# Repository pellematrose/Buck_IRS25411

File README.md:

# Buck_IRS25411
High Voltage Buck featuring IRS25411 LED driver.

The pinheaders offers the opportunity to use it as module on a other PCB.

The IRS25411 is a hysteretic Buck driver for LED applications.
Hysteretic means that there is no fixed frequency but it switches with over and undershooting the threshold level of the feedback pin with the current ripple.
Due to the feedback voltage of 0.5V it is not worth driving more than 1A of current. The needed current sensing resistor results to R = 0.5V / 1A = 0.5Ohms. The power losses are Pls = 0.5V * 1A = 0.5W. This is already to much for a standard 1206 resistor. Using multiple resistors in parallel it might work.

In this design the current sensing resistor moved directly behind the inductor and a op-amp is driving a pnp transistor to provide an appropriate voltage to the feedback pin. Thus, a constant current is maintained.
Additionally, an other part of the circuitry around the TS431 is regulating the voltage.

In parallel operation both CC and CV regulators are active. When the maximum current is flowing the voltage drops and the buck is working in CC mode.
When the maximum current is not flowing the voltage is clipped at the voltage set and the buck is working in CV mode.

The schematic offers the opportunity to assemble the pcb in three ways:
1. Infineon typical application with low side shunt (tested and works)
2. High current CC mode with the op-amp
3. CV mode with TS431 (tested and works)
4. Combined high current CC and CV mode

The design contains a routing mistake:
The connection between VS and Inductor is missing.

Schematics:
1. Infineon typical application with low side shunt

2. High current CC mode with the op-amp

3. CV mode with TS431

4. Combined high current CC and CV mode

To make it easy to adjust some component values the excel file may help you understand how the values are calculated.

I got the main inspiration from various application notes about the buck converter.  
[TI CC CV converter](https://www.ti.com/lit/an/snva829/snva829.pdf)  
[Electronics Stackexchange](https://electronics.stackexchange.com/questions/458384/cc-cv-buck-controller)  
[Buck converter design](https://www.mouser.de/pdfdocs/BuckConverterDesignNote.pdf)

Furthermore, here some links to usefull sites about mosfet losses:  
[Infineon MOSFET Losses Appnote](https://community.infineon.com/gfawx74859/attachments/gfawx74859/MOSFET/285/4/MOSFET%20Power%20Losses%20Calculation%20Using%20the%20Data-Sheet%20Parameters.pdf)  
[Youtube with Dr. K](https://www.youtube.com/watch?v=RViwOc4g-gw)</p>

The Buck design is only tested to 30V input voltage.
If you want to make a real high voltage buck you need to recalculate some components:
- R1 to limit the input current to the driver IC
- Q1, Q2 MOSFET Vds rating
- L1 Inductor
- Supply for the OpAmp (only ratet up to 30V)

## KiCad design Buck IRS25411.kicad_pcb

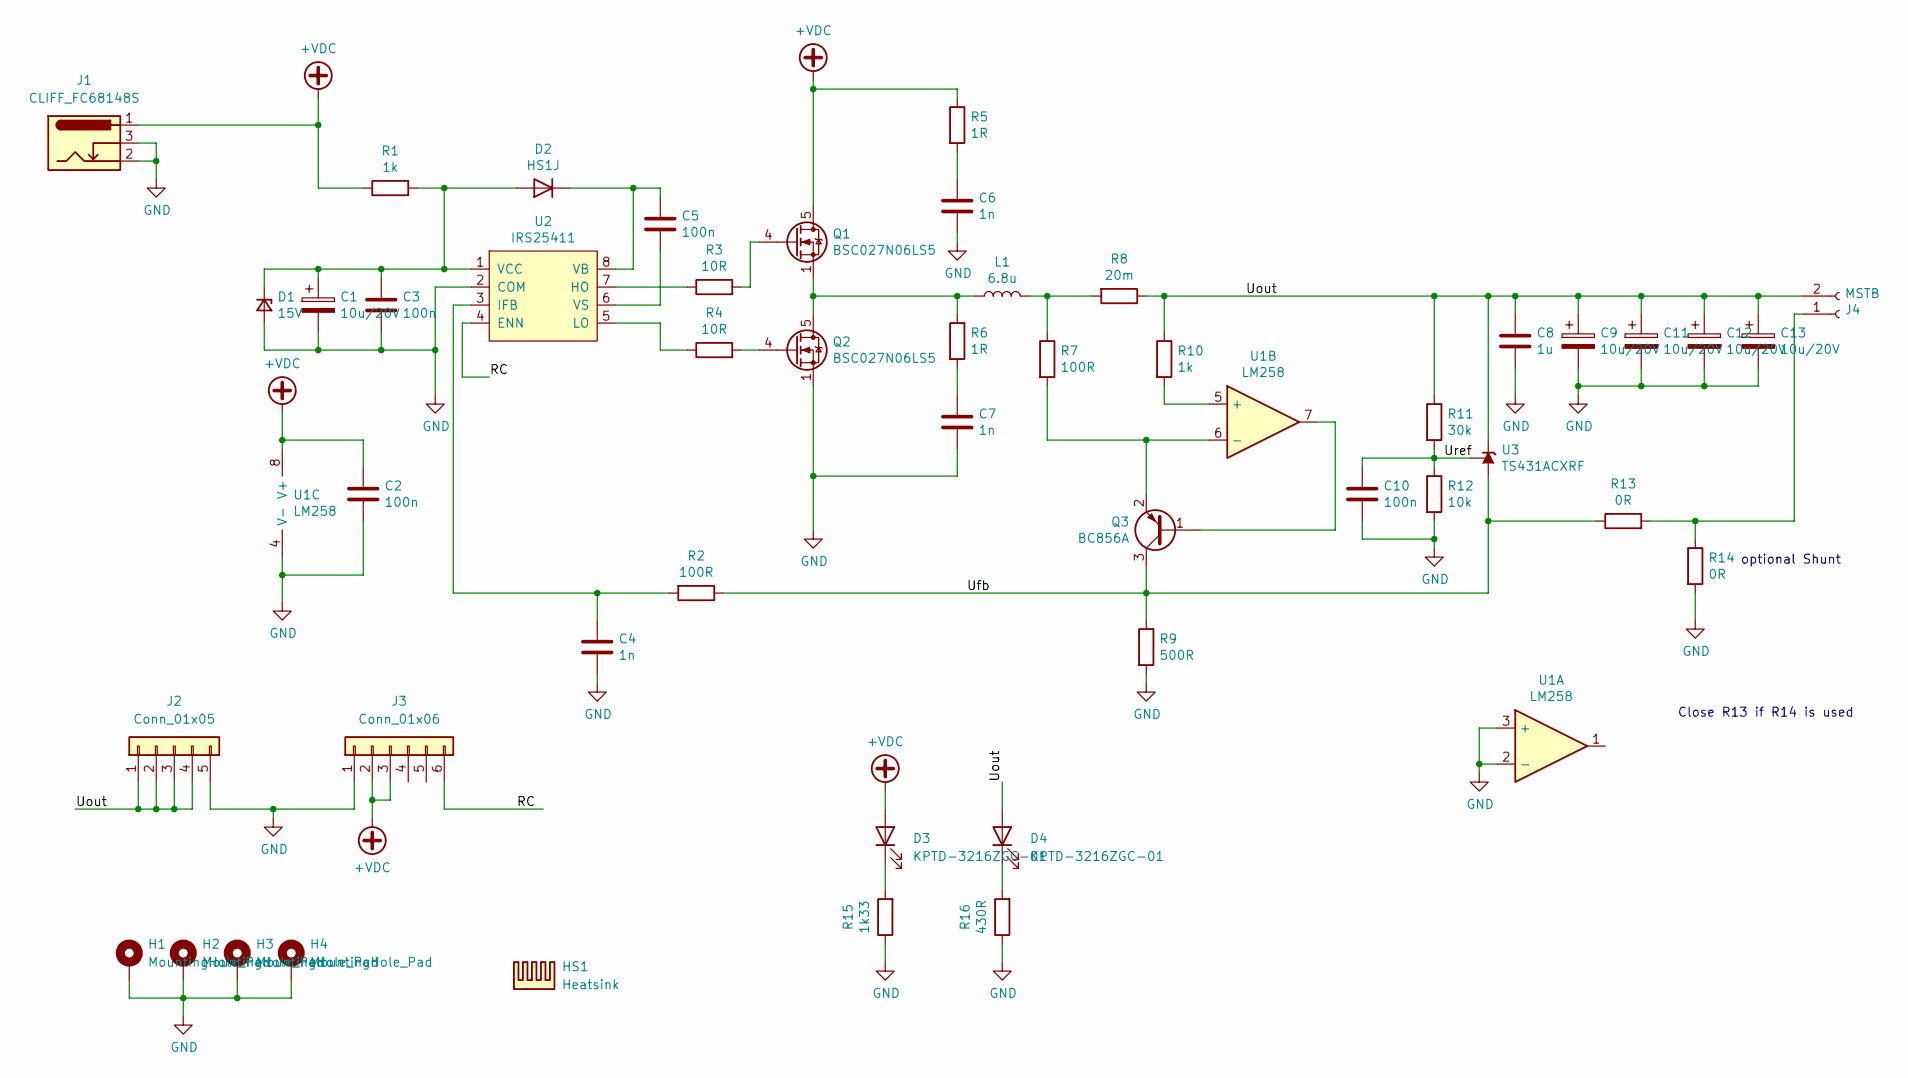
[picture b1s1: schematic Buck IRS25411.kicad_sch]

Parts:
C1, C9, C11, C12, C13: 10u/20V; CP_EIA-3216-18_Kemet-A_Pad1.58x1.35mm_HandSolder
C2, C3, C5, C10: 100n; C_0805_2012Metric_Pad1.18x1.45mm_HandSolder
C4: 1n; C_0603_1608Metric_Pad1.08x0.95mm_HandSolder
C6, C7: 1n; C_1206_3216Metric_Pad1.33x1.80mm_HandSolder
C8: 1u; C_0805_2012Metric_Pad1.18x1.45mm_HandSolder
D1: 15V; D_SOD-123F
D2: HS1J; D_SMA_Handsoldering
D3, D4: KPTD-3216ZGC-01; LED_1206_3216Metric_Pad1.42x1.75mm_HandSolder
H1, H2, H3, H4: MountingHole_Pad; MountingHole_2.2mm_M2_DIN965_Pad_TopBottom
HS1: Heatsink
J1: CLIFF_FC68148S; BarrelJack_CLIFF_FC681465S_SMT_Horizontal
J2: Conn_01x05; PinHeader_1x05_P2.54mm_Horizontal
J3: Conn_01x06; PinHeader_1x06_P2.54mm_Horizontal
J4: MSTB; PhoenixContact_MC_1,5_2-G-5.08_1x02_P5.08mm_Horizontal
L1: 6.8u; L_Bourns_SRR1260
Q1, Q2: BSC027N06LS5; TDSON-8-1
Q3: BC856A; SOT-23
R1, R10: 1k; R_0603_1608Metric_Pad0.98x0.95mm_HandSolder
R2, R7: 100R; R_0603_1608Metric_Pad0.98x0.95mm_HandSolder
R3, R4: 10R; R_0603_1608Metric_Pad0.98x0.95mm_HandSolder
R5, R6: 1R; R_1206_3216Metric_Pad1.30x1.75mm_HandSolder
R8: 20m; R_1206_3216Metric_Pad1.30x1.75mm_HandSolder
R9: 500R; R_0603_1608Metric_Pad0.98x0.95mm_HandSolder
R11: 30k; R_0603_1608Metric_Pad0.98x0.95mm_HandSolder
R12: 10k; R_0603_1608Metric_Pad0.98x0.95mm_HandSolder
R13: 0R; R_0603_1608Metric_Pad0.98x0.95mm_HandSolder
R14: 0R; R_1206_3216Metric_Pad1.30x1.75mm_HandSolder
R15: 1k33; R_0603_1608Metric_Pad0.98x0.95mm_HandSolder
R16: 430R; R_0603_1608Metric_Pad0.98x0.95mm_HandSolder
U1: LM258; SOIC-8_3.9x4.9mm_P1.27mm
U2: IRS25411; SOIC-8_3.9x4.9mm_P1.27mm
U3: TS431ACXRF; SOT-23

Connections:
+VDC: C2.1, D3.2 (A), J1.1, J3.2, J3.3, Q1.5 (D), R1.1, R5.1, U1.8 (V+)
/RC: J3.6, U2.4 (ENN)
/Ufb: Q3.3 (C), R2.1, R9.1, R13.1, U3.3 (A)
/Uout: C8.1, C9.1, C11.1, C12.1, C13.1, D4.2 (A), J2.1, J2.2, J2.3, J2.4, J4.2, R8.1, R10.1, R11.1, U3.2 (K)
/Uref: C10.1, R11.2, R12.1, U3.1 (REF)
GND: C1.2, C2.2, C3.2, C4.2, C6.2, C7.2, C8.2, C9.2, C10.2, C11.2, C12.2, C13.2, D1.2 (A), H1.1, H2.1, H3.1, H4.1, J1.2, J1.3, J2.5, J3.1, Q2.1 (S), Q2.2 (S), Q2.3 (S), R9.2, R12.2, R14.2, R15.1, R16.1, U1.2 (-), U1.3 (+), U1.4 (V-), U2.2 (COM)
unnamed: C1.1, C3.1, D1.1 (K), D2.2 (A), R1.2, U2.1 (VCC)
unnamed: C4.1, R2.2, U2.3 (IFB)
unnamed: C5.1, D2.1 (K), U2.8 (VB)
unnamed: C5.2, U2.6 (VS)
unnamed: C6.1, R5.2
unnamed: C7.1, R6.2
unnamed: D3.1 (K), R15.2
unnamed: D4.1 (K), R16.2
unnamed: J4.1, R13.2, R14.1
unnamed: L1.1, Q1.1 (S), Q1.2 (S), Q1.3 (S), Q2.5 (D), R6.1
unnamed: L1.2, R7.1, R8.2
unnamed: Q1.4 (G), R3.2
unnamed: Q3.1 (B), U1.7
unnamed: Q3.2 (E), R7.2, U1.6 (-)
unnamed: R3.1, U2.7 (HO)
unnamed: R4.1, U2.5 (LO)
unnamed: Q2.4 (G), R4.2
unnamed: R10.2, U1.5 (+)

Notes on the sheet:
Close R13 if R14 is used
optional Shunt

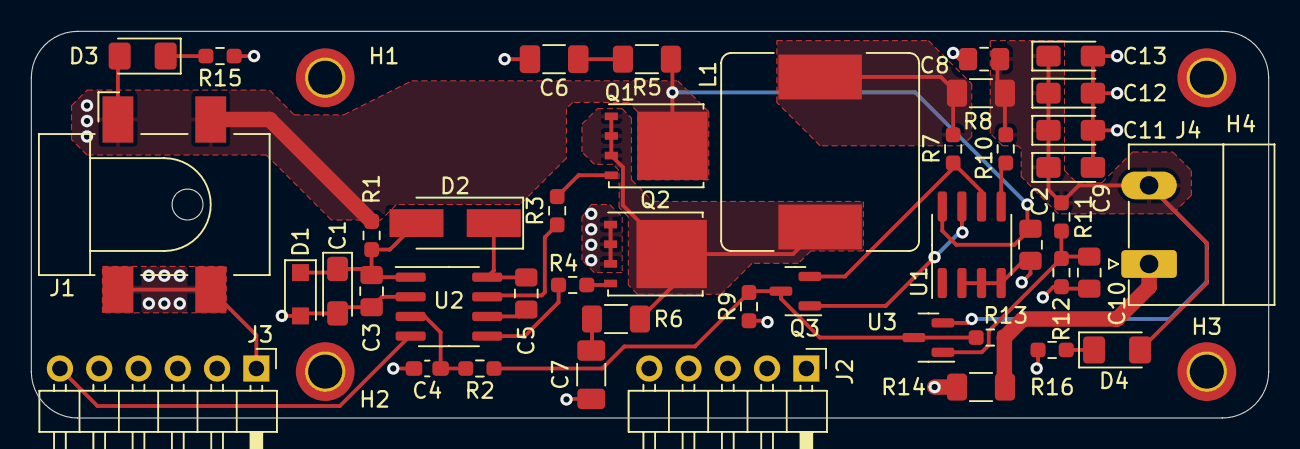
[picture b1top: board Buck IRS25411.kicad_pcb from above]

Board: 2 copper layers, 80.0 x 25.0 mm, 48 parts (0 on the bottom side), 24 nets.

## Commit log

2022-06-17 Update README.md
    starting to write
2022-06-17 Add files via upload
    adding some pictures
2022-06-17 Update README.md
    adding more text
2022-06-17 Update README.md
    more links
2022-06-17 Update README.md
    added more links
2022-06-17 Add files via upload
    added gerber files
2022-06-17 Add files via upload
    Added KiCad files
2022-06-17 Add files via upload
    added schematic pdf
2022-06-17 Add files via upload
    added excel file for calculations
2022-06-17 Add files via upload
    added a picture of the buck
